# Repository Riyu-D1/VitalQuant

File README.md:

# VitalQuant

### Next-generation biological sensing

VitalQuant is an early-stage biotech research project exploring high-sensitivity
biological sensing using photonics, computational methods, and emerging
quantum-inspired techniques. The goal is to investigate whether better
measurement plus better computation can surface subtle biological changes
earlier than conventional approaches.

> **Status:** Early-stage research & prototype development.
> **Not a medical device or diagnostic system** — model outputs are
> experimental anomaly scores only.

## Repository layout

This is the VitalQuant monorepo — all VitalQuant work in one place:

```
hardware/pcb/        fix_v25 board (ESP32-S3-WROOM-1-N16R8) — fix_v24 plus
                     12 probe test points (TP29-TP40, top side, DNP); DRC
                     0 errors / 0 unconnected / 0 shorts / 0 parity, ERC 0,
                     KiCad 10.0.4; fab zip in hardware/pcb/fab/ —
                     see hardware/README.md
hardware/case/       V10 enclosure design (passes CAD checks; nothing
                     printed, no physical fit validation)
                     — layout detail in hardware/README.md
firmware/esp32/      sensor driver contract + hw_v0/hw_v1/hw_v2 profiles
firmware/vitalquant/ firmware v2 for ESP32-S3 (sensors, model, cloud, power)
                     + POSIX host board simulator
web/                 VitalQuant website (Vite + React 19 + Tailwind + three.js)
software/            Python platform + services:
                     src/vitalquant/    core: ingest, processing, ml, quantum, synth, datasets
                     apps/          service entrypoints (FastAPI, pipeline worker, Streamlit)
                     tests/         unit and ingestion test suite
                     supabase/      Postgres DDL migrations (native partitioning)
                     config/        hardware profile examples
                     simulations/   standalone research simulations
                     pyproject.toml, docker-compose.yml, .env.example
docs/                design rationale: spec audit → research → architecture → schema
                     → API → pipeline → ML plan → quantum-sim design → roadmap;
                     docs/FUNDER_SUMMARY.md — one-page status for reviewers
JOURNAL.md           hardware/sensor research log
.github/workflows/   CI
```

## Platform quickstart (local, no hardware)

```bash
pip install -e ".[ingest,processing,ml,dashboard,dev]"
docker compose up -d db                      # local Postgres 17
export DATABASE_URL=postgresql://vitalquant:vitalquant@localhost:5432/vitalquant
vitalquant-migrate                               # apply supabase/migrations
vitalquant-device --label bench-01 --hardware-revision hw_v0   # prints device key once
export VITALQUANT_DEVICE_KEY=vq_...

uvicorn vitalquant.ingest.app:app --port 8000 &  # API
vitalquant-synth --profile config/hardware.example.yaml --duration 120 \
    --api http://localhost:8000              # synthetic device → API → DB
vitalquant-worker --all                          # → quality + features
streamlit run apps/dashboard/app.py          # dashboard
```

## Website

```bash
cd web
npm ci
npm run dev      # Vite dev server
npm run build    # production build → web/dist
```

## License

Source-available for **Hack Club review only** — not open source.
See [LICENSE](LICENSE).

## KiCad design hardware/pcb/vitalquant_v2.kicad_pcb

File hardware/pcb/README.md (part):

# VitalQ hw_v1

Research prototype. This is not a medical device. Nothing here is a claim
about safety, sterility, biocompatibility, or regulatory clearance.
The defibrillator parts are not an IEC 60601-2-27 type-test claim.
The 51 kΩ pulse resistors are a research-prototype attempt to follow
the TI pulse guidance. They do not make this a defibrillator-proof
medical input. The gas-discharge tubes were removed.

The schematic is drawn explicitly. The PCB is a partial route on a
**36.5 × 70.0 mm** rectangle, **4 layers**, parts on both sides.
Six layers were not required. The stackup intent is JLCPCB
JLC04161H-7628, 1.6 mm, 1 oz outer and 0.5 oz inner, ENIG, with POFV
via-in-pad on the BGA balls that can escape. Routing is not finished.
`VERIFICATION.md` lists the nets that are still open.

Regenerate and check with `hardware/pcb/check.sh` (KiCad 10.0.4).

The firmware pin map is `PINMAP.md`. Every resistor and capacitor is
in `PASSIVES.md`. Orderable part numbers are in `vitalq_hw_v1_bom.csv`.
Footprint sources are in `lib/SOURCES.md`.

This branch also carries the `hw_v2` specification (`HW_V2_SPEC.md`).
The files in this directory still describe hw_v1 until the regenerated
schematic and board land; see the hw_v2 paragraph in the Board section
and `VERIFICATION.md` §hw_v2.

## What changed from the previous board

One part was replaced. The XC6206P332MR (U3) is now a TI TPS63802
buck-boost, 3.3 V, with the datasheet 0.47 µH inductor and the 10 µF /
22 µF 0603 capacitors. EN is tied to VBAT so the rail exists before the
I/O expander runs. MODE is grounded (power save). The exposed pad is GND.

J4, the off-board PPG pads, is gone. The ams OSRAM SFH 7072 is on the
board, on the skin side. Anodes go to the TPS61240 5 V rail (TX_5V).
Cathodes go to AFE4900 LED1–LED4. The two photodiodes go to two AFE4900
PD inputs. The package has the optical barrier. The footprint does not
cut a slot through the centre: the 0.9 mm pads at ±0.6 mm would overlap
a slot of 0.8 mm or wider. A window outline stays on User.1.

Everything else that was on the previous board is still here, including
R8 and R10. The list is at the bottom of this file.

## Board

The module antenna keep-out is x = 0 to 6.5 mm, every copper layer.
Pads start at x ≥ 6.55 mm. USB-C is rotated so the opening is the right
edge. The buck-boost, the 5 V boost, and the CP2102 sit on
the top, on the right, next to USB. The charger sits on the bottom,
next to the LiPo pads, away from the TMP117s. The flash, the IMU, the BME280, and
the expander are also on the top, below the module. Analog parts are on
the bottom, away from that switcher column.

Skin side, one cluster: SFH 7072, the
AS7341 with the white LED and the 860 nm LED about 5 mm from the
aperture, and the MLX90632. A 1.0 mm slot separates those LEDs from the
AS7341. J5 and J6 sit on the bottom and top edges of that cluster.
U11 is on a slotted island beside the LEDs. U20 is on the top at the
same XY, outside the module body. The island neck faces the cluster.

Above that cluster, five 2512 pulse resistors (R32–R36) are on the
bottom and four more (R76–R79) are on the top at the same X. The LiPo
pads and the charger are on the bottom, past that row. Four more 2512s
(R80–R83) are the chest bio-impedance leads, on the bottom past the
charger, because a turned 2512 does not fit in the gap that is already
there. There is no gas-discharge tube.

Electrodes are flat solder pads. No headers. J5 is five pads: ADS1292R
positive, ADS1292R negative, RLD, AFE4900 positive, AFE4900 negative.
J6 is the four EDA pads. The EDA cable is a flex tail to the shoulder.
The electrodes on that tail must land at least 5 cm from the ECG
electrodes. That distance is on the harness, not on this board.
J7 is four chest pads for the AD5940 4-wire respiration measurement
(F+, F−, S+, S−). They are not tied to J5 or J6.

The creepage slots between the 2512 electrode pads are 1.0 mm wide,
including the R35–R36 gap and the three gaps between R80–R83. On a
1.6 mm board the path down one face, across the slot, and up the other
face is 4.2 mm. The straight copper gap between adjacent 2512 pads is
still 3.10 mm: five 3.35 mm pads and four wider gaps do not fit in the
36.5 mm width once the antenna keep-out is reserved. J5 is still 0.55 mm
between pads, and J6 and J7 are still 1.05 mm. A custom rule asks for
1.5 mm from each high-voltage electrode net to unrelated copper. DRC
still reports that rule. Adjacent electrode pads are not 1.5 mm apart.

Placement was repacked after review: all 245 parts kept, none removed.
Every skin-facing sensor stays on the bottom in one cluster — the ECG
pads (J5), SFH 7072, MLX90632, AS7341, both LEDs, and the TMP117 pair
sit inside a ~16 × 16 mm window around the same skin spot. The 860 nm
LED (D11) was moved beside the white LED so both emitters light the
same aperture. Each IC's passives were pulled tight against it: the
AFE4900 supply/reference network (C16–C27, C42, R11–R13) wraps U7 on
the bottom, the ADS1292R input/RLD network (R14–R31, R67–R69,
C28–C35, C43, C48–C53, C65–C66) hugs U8, and the AD5940 loop plus the
isolated electrode path (C56–C57, C15, R43–R45, C54–C55, R39–R42,
D6–D9) sit at U6 and along the J6 corridor. U9's I2C pull-ups now
flank the expander, and the USB-UART series resistors moved beside the
connector row. Placement gates are clean: 0 courtyard clashes, 0
pad-to-slot/edge hits, 0 SMD-vs-through-hole hits, 0 missing pads.

The board is partly routed. Freerouting stalled, and a later maze pass
that shorted nets was discarded. `VERIFICATION.md` lists every remaining
unconnected net. Design rules are in `vitalq_hw_v1.kicad_pro` and
`vitalq_hw_v1.kicad_dru`: 0.09 mm is the BGA floor, 0.127 mm is the
clearance outside that area, copper-to-edge is 0.3 mm, and the mask web
is 0.1 mm. Reference designators are hidden. Fab reference text is 0.35 mm.

hw_v2 is specified on this branch (`HW_V2_SPEC.md`, authoritative) and is
**placed but unrouted**; everything above still describes hw_v1. In
short: U1 becomes an ESP32-S3-MINI-1U-N4R2 with a U.FL antenna — the
x < 6.5 mm keep-out strip goes away — and native USB on GPIO19/20 takes
over J1 through the fitted R102/R103 0 Ω straps, while the CP2102 console
stays on UART0 and can take the USB pair instead through the DNP R104/R105
straps (never fit both pairs). Adds: a MAX86178 WLP-49 synchronised ECG/PPG/BioZ
AFE that also drives a satellite-PPG tail (J10), an SHT45 skin RH + temp
sensor at 0x44 on the bottom face, a 730 nm LED (D12) paired with the
AS7341 NIR channel, a distal-temperature tail (J9, sensor at 0x4A), a
RESEARCH-GRADE sweat-electrode site (J11), a DNP unified 14-pos FFC tail
(J12), a DNP ECG pad pair for the MAX86178 (J13), a DNP RTC (0x52), a DNP
PDM mic, and a foam insulation dome over U20 for
the core-temperature trend channel (assembly note only). Nothing is
removed — the defib ladder, TP1–TP28, J8, and the whole power tree stay.
The placed outline is **40.0 × 62.0 mm** (291 parts): it grew 8 mm east
from the ~32 mm target to host the J11/J13 HV-boundary protection row
— J10 and J11 sit on the new east edge, and their 0 Ω cut-points
R118–R122 are 2512 HV-boundary parts like the defib ladder. `check.sh`
passes end-to-end (ERC 0, placement gates 0, 499 unconnected nets plus
9 waived intra-package clearances) but the board is **unrouted and not
fabrication-ready**. Full design doc:
`../../docs/10-hw-v2-upgrade.md`; BOM delta: `BOM_V2_ADDENDUM.md`.

## Part count

**245 parts.** U2 is a BQ25170DSGR in place of the MCP73831. Q3 is
the auto-program pair. D12–D20, the gas-discharge tubes, are gone.
The chest bioZ path adds J7, R80–R87, C67–C70, and D21–D24.
This prefab round adds U21, D25, SW1, SW2, J8, R88–R101, TP1–TP27,
FID1–FID6, H1, and H2.

| Group | Qty | Parts |
| --- | --- | --- |
| ICs | 21 | U1–U21. U2 is BQ25170DSGR. U21 is USBLC6-2SC6 |
| MOSFETs | 2 | Q1 and Q2, both CSD13380F3T |
| Transistor | 1 | Q3 BC847BS,115, SOT-363 |
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
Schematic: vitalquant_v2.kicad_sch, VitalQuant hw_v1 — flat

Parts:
C1, C47: 4.7u; C_0603_1608Metric; LCSC C1705
C2, C20: 4.7u; C_0402_1005Metric; LCSC C23733
C3, C4, C6, C11, C14, C16, C19, C26, C32, C33, C42, C43, C63, C64, C66, C79, C80, C82, C83, C84: 1u; C_0402_1005Metric; LCSC C52923
C7, C45: 22u; C_0603_1608Metric; LCSC C86295
C8, C13, C15, C18, C24, C25, C27, C28, C29, C36, C37, C38, C39, C40, C41, C50, C51, C56, C57, C58, C59, C60, C61, C62, C76, C77, C78, C81, C86, C88, C90, C91: 100n; C_0402_1005Metric; LCSC C1525
C9, C30, C87: 10u; C_0402_1005Metric; LCSC C15525
C10: 1u; C_0603_1608Metric; LCSC C15849
C21, C22, C23, C55, C68, C69, C70: 470n; C_0402_1005Metric; LCSC C47339
C34: 47n; C_0402_1005Metric; LCSC C6261448
C35: 4.7n; C_0402_1005Metric; LCSC C84705
C44, C89: 10u; C_0603_1608Metric; LCSC C19702
C46: 2.2u; C_0402_1005Metric; LCSC C444845
C48, C49, C52, C53: 2.2n; C_0402_1005Metric; LCSC C84703
C54, C67: 15n; C_0402_1005Metric; LCSC C114405
C65: 1.5n; C_0402_1005Metric; LCSC C23967
C85: 47u; C_0603_1608Metric; LCSC C730416
D1, D2, D3, D4, D5, D6, D7, D8, D9, D21, D22, D23, D24, D26, D27, D28: TPD1E10B06; TPD1E10B06_DPY; LCSC C48260
D10: NF2W757G-F1; NF2W757G; Manufacturer_Part_Number NF2W757G-F1
D11: SFH4053; LED_0402_1005Metric; LCSC C2900307
D12: XL0603NRC730; LED_0603_1608Metric
D25: KT-0603G; LED_0603_1608Metric; LCSC C12624
D29, D30: TPD1E10B06; TPD1E10B06_DPY; LCSC C48260; not fitted
D33: 1N5819WS; D_SOD-323; LCSC C191023
FID1, FID2, FID3, FID4, FID5, FID6: FID; Fiducial_1mm
H1, H2: M2; MountingHole_2.2mm_M2
J1: USB-C; USB_C_Receptacle_HRO_TYPE-C-31-M-12; LCSC C165948
J2: LiPo pads; Pads_LiPo
J3: FSR pads; Pads_FSR
J5: ECG pads; Pads_ECG
J6: EDA pads; Pads_EDA
J7: Chest bioZ; Pads_BIOZ
J8: TC2030; Tag-Connect_TC2030-IDC-NL_2x03_P1.27mm_Vertical
J9: I2C tail pads; Pads_1x04
J10: Optical tail pads; Pads_1x06
J11: Sweat site; Pads_1x03
J12: FH12-14S; Hirose_FH12-14S-0.5SH_1x14-1MP_P0.50mm_Horizontal; LCSC C5378715
J13: MX ECG pads; Pads_1x02; not fitted
L1: 0.47u; L_DFE201612E; LCSC C668312
L2: 1.0u; L_DFE201612E; LCSC C337892
Q1, Q2, Q4: CSD13380F3T; Texas_PicoStar_DFN-3_0.69x0.60mm; LCSC C2871092
Q3: BC847BS,115; SOT-363_SC-70-6; Manufacturer_Part_Number BC847BS-7-F; LCSC C156292
Q6: AO3401A; SOT-23; LCSC C15127
R1, R2: 5.1k; R_0402_1005Metric; LCSC C25905
R3: 1.5k; R_0402_1005Metric; LCSC C25867
R5, R6, R7, R8, R9, R11, R14, R49, R52, R53, R60, R65, R67, R68, R69, R70, R71, R72, R73, R74, R98, R100, R101, R112, R113, R115, R116, R117: 10k; R_0402_1005Metric; LCSC C25744
R10, R13, R39, R40, R41, R42, R62, R84, R85, R86, R87: 1k; R_0402_1005Metric; LCSC C11702
R12: 10; R_0402_1005Metric; LCSC C25077
R15, R16, R17: 1M; R_0402_1005Metric; LCSC C26083
R18: 200k; R_0402_1005Metric; LCSC C25764
R19, R20, R21, R22: 2.2k; R_0402_1005Metric; LCSC C25879
R23: 560k; R_0402_1005Metric; LCSC C132339
R24, R25, R44, R46, R48, R50, R59, R99, R110, R123: 100k; R_0402_1005Metric; LCSC C25741
R26, R27, R28, R29: 10M; R_0402_1005Metric; LCSC C26082
R30, R31: 40.2k; R_0402_1005Metric; LCSC C25893
R32, R33, R34, R35, R36, R76, R77, R78, R79, R80, R81, R82, R83, R120, R121, R122: 51k; R_2512_6332Metric; LCSC C30412
R43, R45: 5.11M; R_0402_1005Metric; LCSC C407678
R47, R109: 100; R_0402_1005Metric; LCSC C25076
R51: 150k; R_0402_1005Metric; LCSC C25755
R61: NTC 10k B3380; R_0402_1005Metric; LCSC C77131
R63: 22.1k; R_0402_1005Metric; LCSC C43473
R64: 47.5k; R_0402_1005Metric; LCSC C25896
R66: 301k; R_0402_1005Metric; LCSC C102962
R75: 27.0k; R_0402_1005Metric; LCSC C25771
R88: 150; R_0402_1005Metric; LCSC C25082
R89, R90, R91, R92, R95, R96, R97, R102, R103, R106, R114: 0; R_0402_1005Metric; LCSC C17168
R93: 0; R_0603_1608Metric; LCSC C21189; not fitted
R94: 0; R_0603_1608Metric; LCSC C21189
R104, R105: 0; R_0402_1005Metric; LCSC C17168; not fitted
R107, R108: 100k; R_0402_1005Metric; LCSC C25741; not fitted
R118, R119: 51k; R_2512_6332Metric; LCSC C30412; not fitted
SW1, SW2: TS-1088; SW_SPST_TS-1088-xR020; LCSC C720477
TP1: VBUS; TestPoint_Pad_D1.0mm
TP2: VBAT; TestPoint_Pad_D1.0mm
TP3: +3V3; TestPoint_Pad_D1.0mm
TP4: +1V8; TestPoint_Pad_D1.0mm
TP5: TX_5V; TestPoint_Pad_D1.0mm
TP6: VDD_CP2102; TestPoint_Pad_D1.0mm
TP7, TP8: GND; TestPoint_Pad_D1.0mm
TP9: ESP_EN; TestPoint_Pad_D1.0mm
TP10: ESP_IO0; TestPoint_Pad_D1.0mm
TP11: ESP_TX; TestPoint_Pad_D1.0mm
TP12: ESP_RX; TestPoint_Pad_D1.0mm
TP13: I2C_SDA; TestPoint_Pad_D1.0mm
TP14: I2C_SCL; TestPoint_Pad_D1.0mm
TP15: I2C_SDA_1V8; TestPoint_Pad_D1.0mm
TP16: I2C_SCL_1V8; TestPoint_Pad_D1.0mm
TP17: SPI_SCK; TestPoint_Pad_D1.0mm
TP18: SPI_MOSI; TestPoint_Pad_D1.0mm
TP19: SPI_MISO; TestPoint_Pad_D1.0mm
TP20: CS_ADS1292; TestPoint_Pad_D1.0mm
TP21: CS_AFE4900; TestPoint_Pad_D1.0mm
TP22: CS_AD5940; TestPoint_Pad_D1.0mm
TP23: CS_FLASH; TestPoint_Pad_D1.0mm
TP24: ADS1292_DRDY; TestPoint_Pad_D1.0mm
TP25: AFE4900_ADC_RDY; TestPoint_Pad_D1.0mm
TP26: EXP_INT; TestPoint_Pad_D1.0mm
TP27: CHG_STAT; TestPoint_Pad_D1.0mm
TP28: RTC_INT; TestPoint_Pad_D1.0mm
TP29: RLDREF; TestPoint_Pad_D1.0mm; not fitted
TP30: RLDOUT; TestPoint_Pad_D1.0mm; not fitted
TP31: VBAT_SYS; TestPoint_Pad_D1.0mm; not fitted
TP32: +3V3_ANA; TestPoint_Pad_D1.0mm; not fitted
TP33: TX_5V_RAW; TestPoint_Pad_D1.0mm; not fitted
TP34: RTC_VBK; TestPoint_Pad_D1.0mm; not fitted
TP35: +3V3_ESP; TestPoint_Pad_D1.0mm; not fitted
TP36: IOVDD; TestPoint_Pad_D1.0mm; not fitted
TP37: CHG_ISET; TestPoint_Pad_D1.0mm; not fitted
TP38: CHG_VSET; TestPoint_Pad_D1.0mm; not fitted
TP39: VBUS_DET; TestPoint_Pad_D1.0mm; not fitted
TP40: TS; TestPoint_Pad_D1.0mm; not fitted
U1: ESP32-S3-WROOM-1-N16R8; ESP32_S3_WROOM_1; LCSC C2913202
U2: BQ25170DSGR; Texas_DSG0008A_WSON-8-1EP_2x2mm_P0.5mm_EP0.9x1.6mm; LCSC C5208201
U3: TPS63802DLAR; WSON-10-1EP_2x3mm_P0.5mm_EP0.84x2.4mm; LCSC C2845237
U4: TPS7A2018PDBVR; SOT-23-5; LCSC C963430
U5: CP2102N-A02-GQFN28R; QFN-28-1EP_5x5mm_P0.5mm_EP3.35x3.35mm; LCSC C964632
U6: AFE4900YZR; BGA30N40P5X6_260X210X50; LCSC C2651595
U7: AD5940BCBZ-RL7; BGA56C40P8X7_416X356X55; LCSC C650308
U8: ADS1292RIRSMR; QFN40P400X400X100-33N-D; Manufacturer_Part_Number ADS1292RIRSMR; LCSC C456281
U9: PCA9306DCUR; VSSOP-8_2.3x2mm_P0.5mm; LCSC C33196
U10: AS7341-DLGM; AS7341DLGT; LCSC C2649486
U11, U20: TMP117AIDRVR; TMP117_DRV_NOPASTE; LCSC C699536
U12: MLX90632SLD-DCB-100-RE; MLX90632SLDDCB100SP; Manufacturer_Part_Number MLX90632SLD-DCB-100-RE; LCSC C17235844
U13: BME280; Bosch_LGA-8_2.5x2.5mm_P0.65mm_ClockwisePinNumbering; LCSC C92489
U14: LSM6DSV320XTR; QFN_LSM6DSV80XTR_STM; Manufacturer_Part_Number LSM6DSV320XTR; LCSC C26633007
U15: TPS61240YFFR; TPS61240_YFF; LCSC C2070904
U16: SFH 7072; SFH7072; LCSC C2655172
U17: MAX17048G+T10; TDFN-8-1EP_2x2mm_P0.5mm_EP0.8x1.2mm; LCSC C2682616
U18: W25Q512JVEIQ; W25Q512_WSON8; LCSC C7389628
U19: TCA6408ARSVR; TCA6408A_RSV; LCSC C2649390
U21: USBLC6-2SC6; SOT-23-6; LCSC C7519
U22: MAX86141ENP+; MAX86141_WLP20; LCSC C5328762
U23: SHT45-AD1B; SHT45_DFN4; Manufacturer_Part_Number SHT45-AD1B-R2; LCSC C5221601
U24: RV-3028-C7; RV3028C7; LCSC C2829066
U25: IM69D130; LCSC C536262
U26: SN74AXC2T245RSWR; Texas_RSW0010A_UQFN-10_1.4x1.8mm_P0.4mm; LCSC C1882550

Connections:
+1V8: C36.1, C86.1, C87.1, C88.1, C90.1, R21.1, R22.1, R66.1, R97.2, TP4.1, U9.2 (VREF1), U10.1 (VDD), U22.C2 (VDD_DIG), U22.D2 (VDD_ANA), U26.7 (VCCA), U26.10 (DIR1)
+1V8_LDO: C6.1, R97.1, U4.5 (OUT)
+3V3: C4.1, C37.1, C38.1, C39.1, C40.1, C41.1, C45.1, C59.1, C60.1, C61.1, C76.1, C77.1, C78.1, C81.1, C84.1, C91.1, D10.1 (A), J3.1, J8.1, J9.1, J12.1, R5.1, R6.1, R7.1, R18.1, R19.1, R20.1, R23.1, R47.1, R49.1, R52.1, R53.1, R60.1, R65.1, R74.1, R94.1, R95.1, R98.1, R99.1, R109.1, R112.1, R113.1, R117.1, TP3.1, U3.6 (VOUT), U4.1 (IN), U4.3 (EN), U11.5 (V+), U12.2 (VDD), U13.2 (CSB), U13.6 (VDDIO), U13.8 (VDD), U14.5, U14.8, U14.12, U18.3 (~WP/IO_{2}), U18.7 (~HOLD/~RESET/IO_{3}), U18.8 (VCC), U19.14 (V_{CCP}), U19.15 (V_{CCI}), U20.4 (ADD0), U20.5 (V+), U23.3 (VDD), U24.7 (VDD), U25.2 (VDD), U26.6 (VCCB)
+3V3_ANA: C11.1, C13.1, C16.1, C18.1, C28.1, C29.1, C43.1, C79.1, C80.1, R12.1, R15.1, R26.1, R28.1, R95.2, R116.1, TP32.1, U6.A4 (I2C_SPI_SEL), U6.C1 (RX_SUP), U6.C4 (IO_SUP), U7.A4 (AVDD_1), U7.F2 (AVDD_2), U7.F3 (DVDD), U8.12 (AVDD), U8.14 (CLKSEL), U8.23 (DVDD)
+3V3_ESP: C7.1, C8.1, R94.2, TP35.1, U1.2 (3V3)
AD5940_GPIO0: U1.22 (IO14), U7.F5 (GPIO0)
AD5940_RESET: R11.1, U7.F1 (~RESET), U19.4 (P2)
ADS1292_DRDY: R99.2, TP24.1, U1.38 (IO2), U8.22 (~DRDY)
ADS1292_PWDN: R14.1, U8.15 (~PWDN/~RESET), U19.3 (P1)
ADS_GPIO1: R100.1, U8.26 (GPIO1/RCLK1)
ADS_GPIO2: R101.1, U8.25 (GPIO2/RCLK2)
AFE4900_ADC_RDY: TP25.1, U1.23 (IO21), U6.F4 (ADC_RDY)
AFE4900_RESETZ: R9.1, U6.E1 (RESETZ), U19.2 (P0)
AFE_BG: C15.1, U6.D2 (BG)
AFE_CLK: R10.1, U6.F1 (CLK)
AFE_INM: C57.2, R45.2, U6.A1 (INM_ECG)
AFE_INP: C56.2, R43.2, U6.B1 (INP_ECG)
AFE_N_AC: D5.1, R36.2, R46.1
AFE_N_PAD: J5.5, R36.1
AFE_N_SER: C57.1, R46.2
AFE_P_AC: D4.1, R35.2, R44.1
AFE_P_PAD: J5.4, R35.1
AFE_P_SER: C56.1, R44.2
AIN4_LPF0: C26.1, U7.B4 (AIN4/LPF0)
AVDD_REG: C42.1, U7.D8 (AVDD_REG)
BIOZ_FN: C68.2, U7.D2 (AIN0)
BIOZ_FN_PAD: J7.2, R81.1
BIOZ_FP: R84.2, U7.B3 (AIN1)
BIOZ_FP_PAD: J7.1, R80.1
BIOZ_SN: C70.2, U7.A3 (AIN2)
BIOZ_SN_PAD: J7.4, R83.1
BIOZ_SP: C69.2, U7.B5 (AIN3/BUF_VREF1V8)
BIOZ_SP_PAD: J7.3, R82.1
CE0: R39.2, U7.A7 (CE0)
CE_ISO: C54.2, D6.1, R39.1
CE_SURGE: C54.1, R76.2
CHG_DIS: Q2.1 (G), R59.1, U19.10 (P7)
CHG_ISET: R3.1, TP37.1, U2.2 (ISET)
CHG_PG: R60.2, U1.7 (IO7), U2.6 (~PG)
CHG_STAT: R49.2, TP27.1, U2.5 (STAT), U19.8 (P5)
CHG_VSET: R75.1, TP38.1, U2.7 (VSET)
CP_DTR: Q3.4 (E2), R70.1, U5.28 (~DTR)
CP_RST: R62.2, U5.9 (~RST)
CP_RTS: Q3.1 (E1), R71.1, U5.24 (~RTS)
CP_RX: R72.2, U5.25 (RXD)
CP_TX: R73.1, U5.26 (TXD)
CP_VBUS: R63.2, R64.1, U5.8 (VBUS)
CS_AD5940: R7.2, TP22.1, U1.8 (IO15), U7.F7 (~CS)
CS_ADS1292: R98.2, TP20.1, U1.18 (IO10), U8.18 (~CS)
CS_AFE4900: R116.2, TP21.1, U1.11 (IO18), U6.E3 (SEN)
CS_FLASH: R52.2, TP23.1, U1.9 (IO16), U18.1 (~CS)
CS_MAX86178: R117.2, U1.31 (IO38), U22.A5 (CSB), U26.2 (OE)
DE0: R42.2, U7.B6 (DE0)
DE_SURGE: D9.1, R42.1, R79.2
DVDD_REG: C23.1, U7.G3 (DVDD_REG_1V8)
ECG1_PAD: J5.1, R32.1
ECG2_PAD: J5.2, R33.1
ECG_N: C51.1, C53.1, D2.1, R31.2, R33.2, U8.5 (IN2N)
ECG_P: C50.1, C52.1, D1.1, R30.2, R32.2, U8.6 (IN2P)
EDA_CE_PAD: J6.1, R76.1
EDA_DE_PAD: J6.4, R79.1
EDA_RE_PAD: J6.2, R78.1
EDA_SE_PAD: J6.3, R77.1
ESP_EN: C64.1, J8.5, Q3.6 (C1), R5.2, SW1.1, TP9.1, U1.3 (EN), U19.1 (~RESET)
ESP_IO0: J8.6, Q3.3 (C2), R6.2, SW2.1, TP10.1, U1.27 (IO0)
ESP_RX: J8.4, R73.2, TP12.1, U1.36 (RXD0)
ESP_TX: J8.3, R72.1, TP11.1, U1.37 (TXD0)
EXP_INT: R53.2, TP26.1, U1.15 (IO3), U19.11 (~INT)
FB_3V3: R23.2, R24.1, U3.4 (FB)
FN_ISO: C68.1, D22.1, R85.2
FN_SURGE: R81.2, R85.1
FP_ISO: C67.2, D21.1, R84.1
FP_SURGE: C67.1, R80.2
FSR_ADC: J3.2, R8.1, U1.39 (IO1)
GAUGE_ALRT: R74.2, U1.6 (IO6), U17.5 (ALRT)
GND: C1.2, C2.2, C3.2, C4.2, C6.2, C7.2, C8.2, C9.2, C10.2, C11.2, C13.2, C14.2, C15.2, C16.2, C18.2, C19.2, C20.2, C21.2, C22.2, C23.2, C24.2, C25.2, C26.2, C28.2, C29.2, C30.2, C32.2, C33.2, C36.2, C37.2, C38.2, C39.2, C40.2, C41.2, C42.2, C43.2, C44.2, C45.2, C46.2, C47.2, C48.2, C49.2, C52.2, C53.2, C58.2, C59.2, C60.2, C61.2, C62.2, C63.2, C64.2, C66.2, C76.2, C77.2, C78.2, C79.2, C80.2, C81.2, C82.2, C83.2, C84.2, C85.2, C86.2, C87.2, C88.2, C89.2, C90.2, C91.2, D1.2, D2.2, D3.2, D4.2, D5.2, D6.2, D7.2, D8.2, D9.2, D21.2, D22.2, D23.2, D24.2, D25.2 (K), D26.2, D27.2, D28.2, D29.2, D30.2, J1.A1 (GND), J1.A12 (GND), J1.B1 (GND), J1.B12 (GND), J1.SH (SHIELD), J2.2, J8.2, J9.4, J12.4, Q1.2 (S), Q2.2 (S), Q4.2 (S), R1.2, R2.2, R3.2, R8.2, R9.2, R10.2, R11.2, R14.2, R16.2, R24.2, R25.2, R27.2, R29.2, R48.2, R51.2, R59.2, R61.2, R64.2, R66.2, R75.2, R100.2, R101.2, R108.2, R110.2, R115.2, R123.1, SW1.2, SW2.2, TP7.1, TP8.1, U1.1 (GND), U1.40 (GND), U1.41 (GND), U2.4 (GND), U2.9 (EP), U3.2 (MODE), U3.3 (AGND), U3.8 (GND), U3.11 (EP), U4.2 (GND), U5.3 (GND), U5.29 (GND), U6.B4 (CONTROL1), U6.D1 (RX_GND), U6.D5 (TX_GND), U7.C4 (AGND_1), U7.D5 (AGND_REF)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
I2C_SCL: J9.3, J12.3, R20.2, TP14.1, U1.17 (IO9), U9.6 (SCL2), U11.1 (SCL), U13.4 (SCK), U14.13, U17.7 (SCL), U19.12 (SCL), U20.1 (SCL), U23.2 (SCL), U24.3 (SCL)
I2C_SCL_1V8: R22.2, TP16.1, U9.3 (SCL1), U10.2 (SCL), U12.4 (SCL)
I2C_SDA: J9.2, J12.2, R19.2, TP13.1, U1.12 (IO8), U9.5 (SDA2), U11.6 (SDA), U13.3 (SDI), U14.14, U17.8 (SDA), U19.13 (SDA), U20.6 (SDA), U23.1 (SDA), U24.4 (SDA)
I2C_SDA_1V8: R21.2, TP15.1, U9.4 (SDA1), U10.8 (SDA), U12.1 (SDA)
IN1N: C49.1, R28.2, R29.1, R68.2, U8.3 (IN1N)
IN1N_AC: C51.2, R68.1
IN1P: C48.1, R26.2, R27.1, R67.2, U8.4 (IN1P)
IN1P_AC: C50.2, R67.1
IOVDD: C19.1, R12.2, TP36.1, U7.G2 (IOVDD)
IR_AN: D11.1 (A), R47.2
IR_GATE: Q1.1 (G), R48.1, U19.7 (P4)
IR_K: D11.2 (K), Q1.3 (D)
J11_CE: J11.3, R122.1
J11_RE: J11.2, R121.1
J11_WE: J11.1, R120.1
J13_INM: J13.2, R119.1
J13_INP: J13.1, R118.1
LDR: D10.2 (K), U10.4 (LDR)
LED1_K: J10.1, J12.5, U22.D1 (LED1_DRV)
LED2_K: J10.2, J12.6, U22.C1 (LED2_DRV)
LED3_K: J10.3, J12.7, U22.B1 (LED3_DRV)
LED_A: D25.1 (A), R88.2
LED_AN: J10.4, J12.8, R114.2
LSM6_INT1: U1.4 (IO4), U14.4
MAX86178_INT: R113.2, U1.32 (IO39), U22.B2 (INT)
MIC_CLK: U1.33 (IO40), U25.3 (CLOCK)
MIC_DAT: U1.34 (IO41), U25.1 (DATA)
MISO_AD: R91.1, U7.E8 (MISO)
MISO_ADS: R89.1, U8.21 (DOUT)
MISO_AFE: R90.1, U6.E2 (SDOUT)
MISO_FL: R92.1, U18.2 (DO/IO_{1})
MISO_MX: R106.1, U26.5 (B1)
MX_ECG_INM: D30.1, R119.2
MX_ECG_INP: D29.1, R118.2
MX_SDO_1V8: U22.A3 (SDO), U26.8 (A1)
MX_VREF: C83.1, U22.B5 (VREF)
NIR730_GATE: Q4.1 (G), R110.1, U7.E1 (GPIO2)
NIR_AN: D12.1 (A), R109.2
NIR_K: D12.2 (K), Q4.3 (D)
PD2_INM: U6.B3 (INM2), U16.10 (PD2_A)
PD2_INP: U6.B2 (INP2), U16.3 (PD2_C)
PD_A: J10.6, J12.10, U22.C5 (PD_GND)
PD_INM: U6.A3 (INM), U16.2 (PD1_A)
PD_INP: U6.A2 (INP), U16.1 (PD1_C)
PD_K: J10.5, J12.9, U22.D5 (PD1_IN)
PGA1N: C34.1, U8.1 (PGA1N)
PGA1P: C34.2, U8.2 (PGA1P)
PGA2N: C35.1, U8.7 (PGA2N)
PGA2P: C35.2, U8.8 (PGA2P)
Q3_B1: Q3.2 (B1), R70.2
Q3_B2: Q3.5 (B2), R71.2
RC0_0: C27.1, U7.C8 (RC0_0)
RC0_1: C27.2, U7.B8 (RC0_1)
RCAL0: R13.1, U7.C1 (RCAL0)
RCAL1: R13.2, U7.B1 (RCAL1)
RE0: R41.2, U7.A8 (RE0)
RESP_MODN: R31.1, U8.32 (RESP_MODN/IN3N)
RESP_MODP: R30.1, U8.31 (RESP_MODP/IN3P)
RE_SURGE: D8.1, R41.1, R78.2
RLDINV: C65.2, R17.2, U8.28 (RLDINV)
RLDOUT: C65.1, R17.1, R43.1, R45.1, R69.2, TP30.1, U8.30 (RLDOUT)
RLDREF: C66.1, R15.2, R16.1, TP29.1, U8.29 (RLDIN/RLDREF)
RLD_CLAMP: D3.1, R34.2, R69.1
RLD_PAD: J5.3, R34.1
RTC_INT: R112.2, TP28.1, U24.2 (INT)
RTC_VBK: R115.1, TP34.1, U24.6 (VBACKUP)
SE0: C55.2, U7.A6 (SE0)
SE_ISO: C55.1, D7.1, R40.2
SE_SURGE: R40.1, R77.2
SN_ISO: C70.1, D24.1, R87.2
SN_SURGE: R83.2, R87.1
SPARE_IN: R107.2, R108.1, U1.35 (IO42)
SPI_MISO: R89.2, R90.2, R91.2, R92.2, R106.2, TP19.1, U1.21 (IO13)
SPI_MOSI: TP18.1, U1.19 (IO11), U6.F2 (I2C_DAT), U7.E7 (MOSI), U8.19 (DIN), U18.5 (DI/IO_{0}), U22.A4 (SDI)
SPI_SCK: TP17.1, U1.20 (IO12), U6.F3 (I2C_CLK), U7.F8 (SCLK), U8.20 (SCLK), U18.6 (CLK), U22.A2 (SCLK)
SP_ISO: C69.1, D23.1, R86.2
SP_SURGE: R82.2, R86.1
STATUS_LED: R88.1, U1.10 (IO17)
SWEAT_CE: D28.1, J12.13, R122.2, U7.A1 (AFE4)
SWEAT_RE: D27.1, J12.12, R121.2, U7.A2 (AFE3)
SWEAT_WE: D26.1, J12.11, R120.2, U7.C5 (AIN6)
SW_L1: L1.1, U3.9 (L1)
SW_L2: L1.2, U3.7 (L2)
TMP117_ALERT: R65.2, U1.5 (IO5), U11.3 (ALERT)
TS: J2.3, Q2.3 (D), R61.1, TP40.1, U2.3 (TS)
TX1: U6.D4 (TX1), U16.6 (G1_C)
TX2: U6.E5 (TX2), U16.12 (G2_C)
TX3: U6.E4 (TX3), U16.8 (R_C)
TX4: U6.C5 (TX4), U16.9 (IR_C)
TX5_EN: R25.1, U15.C1 (EN), U19.5 (P3)
TX_5V: C14.1, C89.1, R96.2, R114.1, TP5.1, U6.F5 (TX_SUP), U16.4 (IR_A), U16.5 (G1_A), U16.7 (R_A), U16.11 (G2_A), U22.A1 (VLED)
TX_5V_RAW: C47.1, R96.1, TP33.1, U15.B2 (VOUT), U15.C2 (FB)
TX_SW: L2.2, U15.B1 (L)
USB_CC1: J1.A5 (CC1), R1.1
USB_CC2: J1.B5 (CC2), R2.1
USB_DM: J1.A7 (D-), J1.B7 (D-), R103.1, R105.1, U21.3 (IO2), U21.4 (IO2)
USB_DM_CP: R105.2, U5.5 (D-)
USB_DM_S3: R103.2, U1.13 (IO19)
USB_DP: J1.A6 (D+), J1.B6 (D+), R102.1, R104.1, U21.1 (IO1), U21.6 (IO1)
USB_DP_CP: R104.2, U5.4 (D+)
USB_DP_S3: R102.2, U1.14 (IO20)
VBAT: C2.1, C3.1, C58.1, C82.1, C85.1, J2.1, Q6.3 (D), R93.1, R107.1, TP2.1, U2.8 (OUT), U17.2 (CELL), U17.3 (VDD)
VBAT_SYS: C44.1, C46.1, D33.1 (K), L2.1, Q6.2 (S), R93.2, TP31.1, U3.1 (EN), U3.10 (VIN), U15.A1 (VIN)
VBIAS0: C25.1, U7.C7 (VBIAS0)
VBIAS_CAP: C22.1, U7.D1 (VBIAS_CAP)
VBUS: C1.1, C10.1, C63.1, D33.2 (A), J1.A4 (VBUS), J1.A9 (VBUS), J1.B4 (VBUS), J1.B9 (VBUS), Q6.1 (G), R50.1, R63.1, R123.2, TP1.1, U2.1 (IN), U5.7 (VREGIN), U21.5 (VBUS)
VBUS_DET: R50.2, R51.1, TP39.1, U19.9 (P6)
VCAP1: C32.1, U8.11 (VCAP1)
VCAP2: C33.1, U8.27 (VCAP2)
VDD_CP2102: C9.1, C62.1, R62.1, TP6.1, U5.1 (~DCD), U5.2 (~RI/CLK), U5.6 (VDD), U5.23 (~CTS), U5.27 (~DSR)
VREF2: R18.2, U9.7 (VREF2), U9.8 (EN)
VREFP: C30.1, U8.9 (VREFP)
VREF_1V82: C20.1, U7.A5 (VREF_1V82)
VREF_2V5: C21.1, U7.D7 (VREF_2V5)
VZERO0: C24.1, U7.B7 (VZERO0)

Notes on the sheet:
J13 DNP pads: optional second ECG input pair. R118/R119 + D29/D30 fitted.
J10: LED1/2/3 cathodes, LED anode, PD cathode, PD anode.
I2C and IMU
R13 is RCAL. C27 sits between RC0_0 and RC0_1. XTAL pins are open: the internal oscillator is used.
U23 SHT45-AD1B, 0x44, skin side.
Alternate strap (DNP): move 0R to R104/R105 for the CP2102 bridge.
LED_AN ties to TX_5V through R114 (5 V headroom for green/satellite emitters).
Decoupling, RCAL, RC0
Sheets below contain the parts. They are not empty stubs.
Module decoupling
USB-C, LiPo charger, 3.3 V rail, 1.8 V rail
J12 DNP FFC: pins 1-4 = J9 order, 5-10 = J10 order, 11-13 = J11 order, 14 open.
Charge is on whenever USB is present and TS is in range. CHG_DIS high shorts TS and stops it.
Left: 1.8 V AS7341 behind PCA9306. Right: 3.3 V bus, including the IMU.
Q3 is the DevKitC auto-program pair: DTR/RTS to EN and GPIO0. R70 and R71 are the 10k bases.
Decoupling
POWER & CHARGING (root sheet)
ESP32-S3-WROOM-1-N16R8. On-board PCB antenna: antenna end overhangs the board edge; all-layer keep-out under the on-board sliver. 16 MB flash + 8 MB octal PSRAM inside; IO35/36/37 reserved NC.
I2C sensors and IMU
Test and debug
U3 is a TPS63802 buck-boost. R23/R24 set 3.30 V. C44 and C45 are the datasheet 0603 ceramics. C3 and C4 stay.
D12 is the 730 nm LED; Q4 gate is AD5940 GPIO2 (E1). Pairs with the AS7341 NIR channel.
U4 is the 1.8 V LDO, fed from U3, EN tied to IN. AS7341 VDD is 1.7-2.0 V. Other ICs are 3.3 V.
R61 stays DNP. Fit the cell NTC, not R61 as well. R3 is 1.5k, so charge current is 200 mA.
Straps and FSR
Bias and decoupling
IO26 is the in-module PSRAM select on N4R2. IO33-37, IO47, IO48 are spare GPIO, left open.
AFE4900 PPG and second ECG lead
J7 is F+ F- S+ S-. Dedicated chest pads. Not paralleled onto J5 or J6.
J11 sweat site — RESEARCH-GRADE. WE=AIN6(C5), RE=AFE3(A2), CE=AFE4(A1); VERIFY switch matrix.
MCU
hw_v2: AIN6/AFE3/AFE4 feed J11 (RESEARCH-GRADE sweat site) and GPIO2 is NIR730_GATE. Other GPIO balls stay open.
C16 AVDD, C18 DVDD, C42 AVDD_REG, C19 IOVDD after R12, C20-C26 are the reference and bias caps.
EN has R5 10k and C64 1 uF. Q3 on the USB sheet is the DTR/RTS auto-program pair.
U5/U21/Q3 are unchanged. CP2102 keeps UART0 on ESP_TX/ESP_RX.
Fitted: J1 -> S3 IO20/IO19 (native USB, on-chip JTAG+console).
Other sheets
MAX86178 and tails
J8 Tag-Connect TC2030-NL: 1 +3V3, 2 GND, 3 ESP_TX, 4 ESP_RX, 5 EN, 6 IO0.
U25 IM69D130. PDM on IO40/IO41. 100 nF on VDD (datasheet).

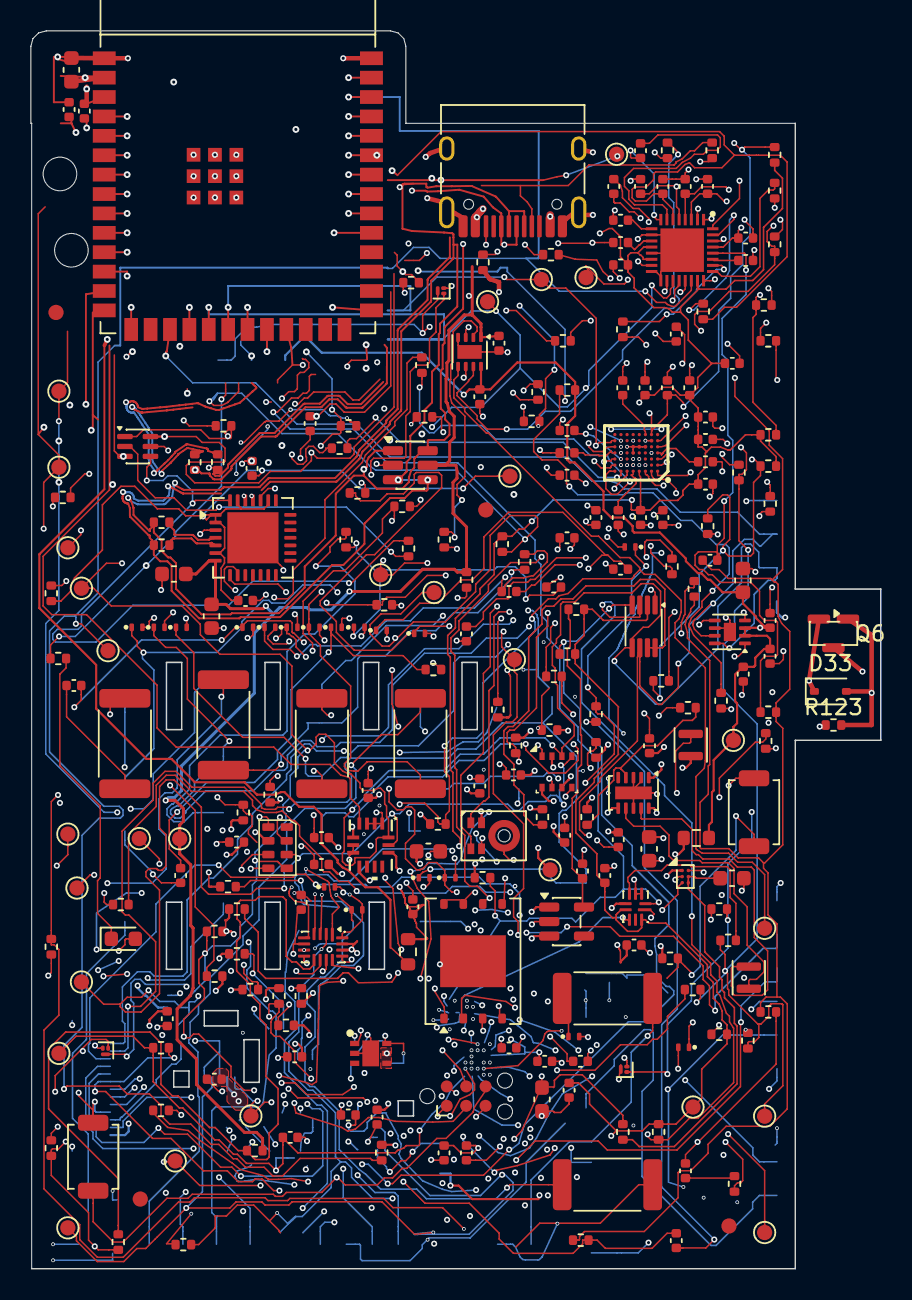
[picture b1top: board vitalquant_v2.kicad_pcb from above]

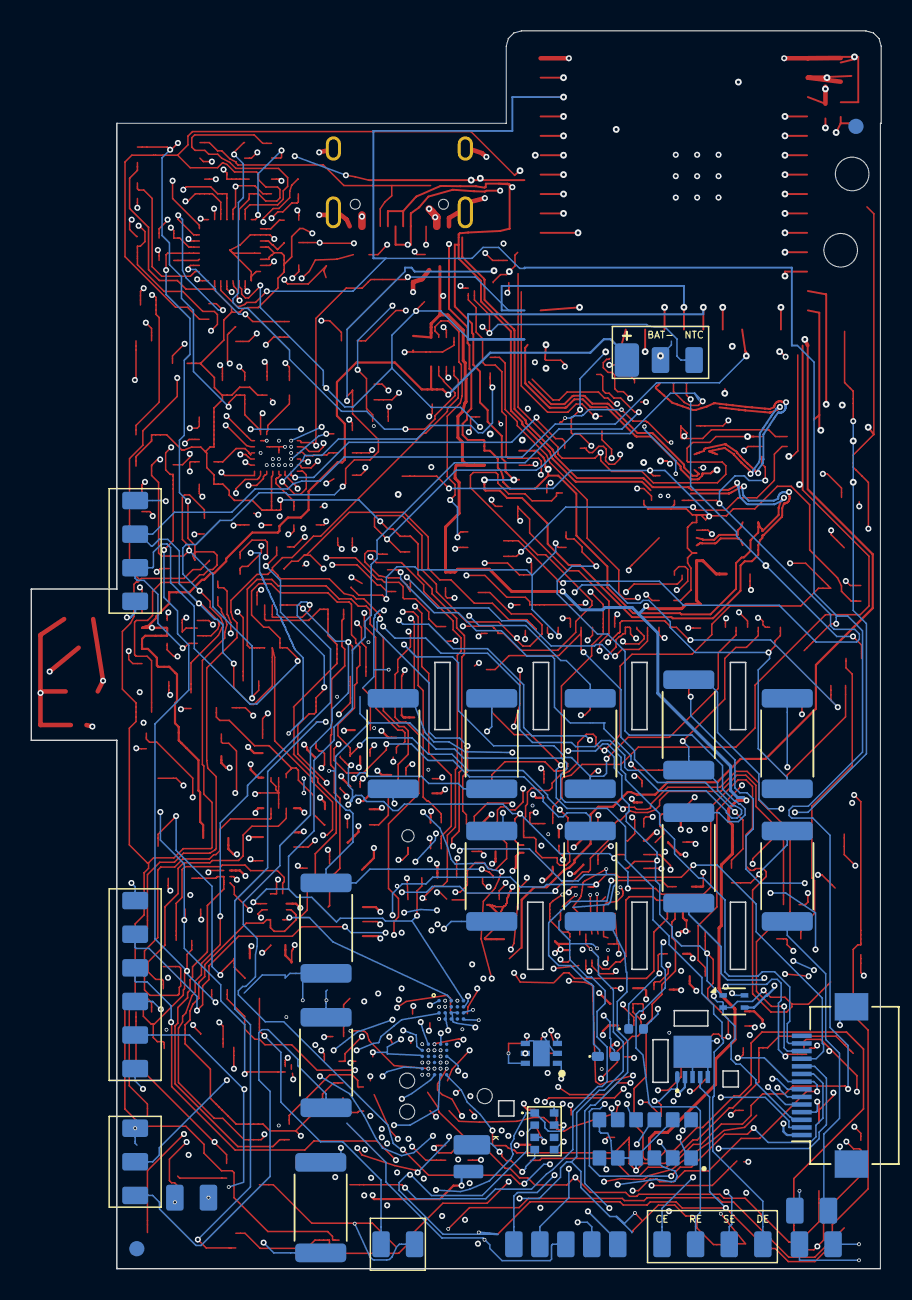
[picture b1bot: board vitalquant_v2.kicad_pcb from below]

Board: 8 copper layers, 55.6 x 81.0 mm, 302 parts (35 on the bottom side), 191 nets.

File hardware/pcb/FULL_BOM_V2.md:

# hw_v2 — Full Board BOM (every component)

292 placed parts on `devin/hw-v2-pcb`. Per single board.
"DNP" = designed in but not populated at assembly.

## ICs & modules — 25

| Ref | Part (orderable MPN) | Package | LCSC | Notes |
|---|---|---|---|---|
| U1 | ESP32-S3-MINI-1-N4R2 | Module 15.4×20.5 | C3013941 | MCU, integrated antenna |
| U2 | BQ25170DSGR | WSON-8 | — | LiPo charger |
| U3 | TPS63802DLAR | WSON-10 | — | Buck-boost +3V3 |
| U4 | TPS7A2018PDBVR | SOT-23-5 | — | 1.8 V LDO |
| U5 | CP2102N-A02-GQFN28R | QFN-28 | — | USB-UART (strap option) |
| U6 | AFE4900YZR | BGA-30 | — | PPG/SpO2 AFE |
| U7 | AD5940BCBZ-RL7 | BGA-56 | C650308 | EDA/BioZ potentiostat |
| U8 | ADS1292RIRSMT | QFN-33 | C882777 | ECG AFE |
| U9 | PCA9306DCUR | VSSOP-8 | — | I2C level shifter |
| U10 | AS7341-DLGM | OLGA-8 | — | Spectral sensor |
| U11, U20 | TMP117AIDRVR | DRV-6 | — | Skin + ambient temp ×2 |
| U12 | MLX90632SLD-DCB-100-SP | SFN-5 | — | IR temperature |
| U13 | BME280 | LGA-8 | — | Ambient P/RH/T |
| U14 | LSM6DSV80XTR | LGA-14 | — | IMU |
| U15 | TPS61240YFFR | DSBGA-6 | — | TX_5V boost |
| U16 | SFH 7072 | Module | C2655172 | Optical emitter+PD |
| U17 | MAX17048G+T10 | TDFN-8 | C2682616 | Fuel gauge |
| U18 | W25Q512JVEIQ | WSON-8 | — | 512 Mbit flash |
| U19 | TCA6408ARSVR | UQFN-8 | C2649390 | GPIO expander |
| U21 | USBLC6-2SC6 | SOT-23-6 | C7519 | USB ESD array |
| U22 | MAX86178ENJ+ | WLP-49 | — | ECG/PPG/BioZ AFE (NDA part) |
| U23 | SHT45-AD1B(-R2) | DFN-4 | — | Humidity/temp |
| U24 | RV-3028-C7 | SON-8 | — | RTC |
| U25 | IM69D130V01XTSA1 | LLGA-5 | — | PDM mic (fitted) |

## Optical emitters — 4

| Ref | Part | Pkg | Qty |
|---|---|---|---|
| D10 | NF2W757G-F1 white LED | NF2W757G | 1 |
| D11 | SFH 4053 IR emitter | 0402 | 1 |
| D12 | SFH 4735 730 nm NIR | 0402 | 1 |
| D25 | KT-0603G green status LED | 0603 | 1 (C12624) |

## ESD / protection — 19

| Part | Refs | Qty fitted | DNP |
|---|---|---|---|
| TPD1E10B06DPYR | D1–D9, D21–D30 | 18 | 0 |
| USBLC6-2SC6 | (listed above, U21) | — | — |

## Connectors / switches — 4 orderable

| Ref | Part | Qty | Status |
|---|---|---|---|
| J1 | TYPE-C-31-M-12 USB-C receptacle | 1 | Fitted |
| J12 | FH12-14S-0.5SH(55) FFC-14 | 1 | DNP |
| SW1, SW2 | TS-1088-AR02016 tactile | 2 | Fitted (C720477) |
| J2,J3,J5,J6,J7,J8,J9,J10,J11,J13 | Solder pads / TC2030 footprint | — | Board features, no orderable part |

## Magnetics — 2

| Ref | Part | Value |
|---|---|---|
| L1 | DFE201612E-R47M | 0.47 µH |
| L2 | DFE201612E-1R0M | 1.0 µH |

## Transistors — 4

| Ref | Part | LCSC |
|---|---|---|
| Q1, Q2, Q4 | CSD13380F3T N-FET PicoStar ×3 | C2871092 |
| Q3 | BC847BS,115 dual NPN SOT-363 | — |

## Capacitors — 72

| MPN | Value / Pkg | Qty fit | DNP | Refs |
|---|---|---|---|---|
| GRM155R71C104KA88 | 100 nF / 0402 | 30 | 0 | C8,C13,C15,C18,C24,C25,C27–C29,C36–C41,C50,C51,C56–C63,C76–C79,C81 |
| GRM155R61A105KE15 | 1 µF / 0402 | 18 | 0 | C3,C4,C6,C11,C14,C16,C19,C26,C32,C33,C42,C43,C64,C66,C80,C82,C83,C84 |
| GRM155R61A474KE15 | 470 nF / 0402 | 7 | 0 | C21–C23,C55,C68–C70 |
| GRM1555C1H222JA01 | 2.2 nF / 0402 | 4 | 0 | C48,C49,C52,C53 |
| GRM155R60J475ME87 | 4.7 µF / 0402 | 3 | 0 | C2,C9,C20 |
| GRM155R71H153KA12 | 15 nF / 0402 | 2 | 0 | C54,C67 |
| CL10A476MQ8NRNC | 47 µF / 0603 | 1 | 0 | C85 (C19702) |
| CL10A226MQ8NRNC | 22 µF / 0603 | 1 | 0 | C7 (C59461) |
| GRM188R61A226ME15 | 22 µF / 0603 | 1 | 0 | C45 |
| CL10A475KA8NQNC | 4.7 µF / 0603 | 1 | 0 | C1 (C69335) |
| GRM188R61A475KE15 | 4.7 µF / 0603 | 1 | 0 | C47 |
| GRM188R61A106ME69 | 10 µF / 0603 | 1 | 0 | C44 |
| GRM155R60J106ME05 | 10 µF / 0402 | 1 | 0 | C30 |
| CL10A105KA8NNNC | 1 µF / 0603 | 1 | 0 | C10 |
| GRM155R60J225ME15 | 2.2 µF / 0402 | 1 | 0 | C46 |
| GRM155R71H473KA88 | 47 nF / 0402 | 1 | 0 | C34 |
| GRM1555C1H472JA01 | 4.7 nF / 0402 | 1 | 0 | C35 |
| GRM1555C1H152JA01 | 1.5 nF / 0402 | 1 | 0 | C65 |

## Resistors — 96

| MPN | Value / Pkg | Qty fit | DNP | Refs |
|---|---|---|---|---|
| RC0402FR-0710KL | 10 kΩ / 0402 | 26 | 0 | R5–R9,R11,R14,R49,R52,R53,R60,R65,R67–R71,R74,R98,R100,R101,R112,R113,R115,R116,R117 (C25744) |
| RC0402FR-071KL | 1 kΩ / 0402 | 14 | 0 | R10,R13,R39–R42,R62,R72,R73,R84–R88 (C11702) |
| DPCR2512-51KJT18 | 51 kΩ / 2512 | 13 | 0 | R32–R36, R76–R83 (HV ladder) |
| 0402WGF0000TCE | 0 Ω / 0402 | 11 | 2 | R89–R92,R95–R97,R102,R103,R106,R114 (+R104,R105) C17168 |
| RC0402FR-07100KL | 100 kΩ / 0402 | 9 | 2 | R24,R25,R44,R46,R48,R50,R59,R99,R110 (+R107,R108) C25741 |
| 25121WJ0000T4E | 0 Ω / 2512 | 5 | 0 | R118–R122 (HV cut-points) C2908946 |
| RC0402FR-074K7L | 4.7 kΩ / 0402 | 4 | 0 | R19–R22 |
| 0402WGF1005TCE | 10 MΩ / 0402 | 4 | 0 | R26–R29 (C26082) |
| RC0402FR-071ML | 1 MΩ / 0402 | 3 | 0 | R15–R17 |
| RC0402FR-075K1L | 5.1 kΩ / 0402 | 2 | 0 | R1,R2 |
| RC0402FR-0740K2L | 40.2 kΩ / 0402 | 2 | 0 | R30,R31 |
| RC0402FR-075M11L | 5.11 MΩ / 0402 | 2 | 0 | R43,R45 |
| RC0402FR-07100RL | 100 Ω / 0402 | 2 | 0 | R47,R109 |
| RC0402FR-07200KL | 200 kΩ / 0402 | 2 | 0 | R18,R51 |
| 0603WAF0000T5E | 0 Ω / 0603 | 2 | 0 | R93,R94 (C21189) |
| RC0402FR-0710RL | 10 Ω / 0402 | 1 | 0 | R12 |
| 0402WGF1501TCE | 1.5 kΩ / 0402 | 1 | 0 | R3 (C25867) |
| RC0402FR-07560KL | 560 kΩ / 0402 | 1 | 0 | R23 |
| NCU15XH103F6SRC | 10 kΩ NTC / 0402 | 0 | 1 | R61 (DNP — cell NTC option) |
| RC0402FR-0722K1L | 22.1 kΩ / 0402 | 1 | 0 | R63 |
| RC0402FR-0747K5L | 47.5 kΩ / 0402 | 1 | 0 | R64 |
| RC0402FR-07301KL | 301 kΩ / 0402 | 1 | 0 | R66 |
| RC0402FR-0727KL | 27 kΩ / 0402 | 1 | 0 | R75 |

## Board features (no part to buy)

- TP1–TP28 test-point pads (28)
- FID1–FID6 fiducials (6)
- H1, H2 M2 mounting holes
- J2/J3/J5/J6/J7/J9/J10/J11/J13 solder-pad fields, J8 TC2030 pads

## Distinct orderable line items: 57
## Totals per board: 285 fitted + 7 DNP placements
(Remaining DNP — all intentional options: R61 cell-NTC, R104/R105 CP2102 USB strap
(mutually exclusive with R102/R103), R107/R108 SPARE divider, J12 FFC, J13 pads)

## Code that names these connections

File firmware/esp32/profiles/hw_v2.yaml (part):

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# ESP32-WROOM-32E → ESP32-S3-MINI-1U-N4R2 (4 MB flash + 2 MB PSRAM, U.FL antenna).
#
# GPIO map (S3-MINI-1U, per spec interface table):
#   GPIO1  FSR_ADC (ADC1_CH0)          GPIO2  ADS1292_DRDY  (timestamped input)
#   GPIO3  EXP_INT (TCA6408, strap)    GPIO4  LSM6_INT1
#   GPIO5  TMP117_ALERT                GPIO6  GAUGE_ALRT
#   GPIO7  CHG_PG                      GPIO8/9  I2C_SDA / I2C_SCL (I2C3V3)
#   GPIO10 CS_ADS1292                  GPIO11/12/13  SPI_MOSI / SPI_SCK / SPI_MISO
#   GPIO14 AD5940_GPIO0 (AD5940 ball F5)  GPIO15 CS_AD5940
#   GPIO16 CS_FLASH (W25Q512)          GPIO17 STATUS_LED (via R88)
#   GPIO18 CS_AFE4900                  GPIO19/20 USB_D- / USB_D+ (native USB-CDC → J1)
#   GPIO21 AFE4900_ADC_RDY (timestamped input)
#   GPIO38 CS_MAX86178                 GPIO39 MAX86178_INT (timestamped input)
#   GPIO40/41 MIC_CLK / MIC_DAT (DNP)  GPIO42 SPARE_IN (digital-only, no ADC — spare input)
#   GPIO43/44 UART0_TX / UART0_RX → CP2102N console (kept)
#   ESP_IO0 / ESP_EN: module pins (SW1/SW2, TP10/TP9; TP24 = ADS1292_DRDY)
#
# USB: native USB-CDC on GPIO19/20 is the DEFAULT strap — R102/R103 (0Ω,
# fitted) route J1 D+/D- to USB_DP_S3/USB_DM_S3. Alternate strap R104/R105
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#   P4 IR_GATE, P5 CHG_STAT, P6 VBUS_DET, P7 CHG_DIS
#
# NIR730_GATE: D12 730 nm LED (+3V3 via R109 100Ω) cathode switched by Q4,
# gated by AD5940 GPIO2 on ball E1 — NOT GPIO0 (GPIO0/ball F5 is the ESP32
# GPIO14 input link, net AD5940_GPIO0). Pairs with the AS7341 nir channel
# for the derived tissue.sto2 ratio.
#
# Tail connectors:
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    model: ADS1292R             # ECG + respiration; defib-protection ladder kept
    bus: spi1
    cs: 10                      # CS_ADS1292
    int_pin: 2                  # ADS1292_DRDY — timestamped input
    outputs: [ecg.ii, resp.waveform]
    sample_rate_hz: 500

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    model: AFE4900              # main SpO2 PPG → SFH7072 optical front-end (kept)
    bus: spi1
    cs: 18                      # CS_AFE4900
    int_pin: 21                 # AFE4900_ADC_RDY — timestamped input
    channels:
      - { id: ppg.red, wavelength_nm: 660, led_driver: 1, pd: 0 }
      - { id: ppg.ir,  wavelength_nm: 940, led_driver: 2, pd: 1 }
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    model: MAX86178             # synchronized ECG/PPG/BioZ AFE; hw_v2 duty = satellite PPG tail J10
    bus: spi1
    cs: 38                      # CS_MAX86178
    int_pin: 39                 # MAX86178_INT — timestamped input
    channels:
      # SFH7050A emitters on J10 time-mux onto the single ppg.satellite stream;
      # led_driver = MAX86178 LED1/2/3 cathode pad. VERIFY wavelength set vs BOM.
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    model: AD5940               # EDA / bioZ-lactate duty (kept); reset via expander P2
    bus: spi1
    cs: 15                      # CS_AD5940
    # also owns NIR730_GATE — AD5940 GPIO2 on ball E1 (not GPIO0/ball F5)
    outputs: []                 # EDA/bioZ waveform channel ids pending registration

  sweat:
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                                # three: 0x48 U11 skin, 0x49 U20 under the
                                # insulation dome (ZHF pair → core.temp_est),
                                # 0x4A distal on J9 tail → skin.temp_distal.
                                # TMP117_ALERT = GPIO5
    outputs: [core.temp_est, skin.temp_distal]
    rate_hz: 1

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  contact:
    enabled: true
    model: FSR402               # kept — FSR pads
    input: adc1_ch0             # FSR_ADC = GPIO1 — ordinal level, no SI units
    outputs: [contact.level]
    rate_hz: 20

  gauge:
    enabled: true
    model: MAX17048             # fuel gauge, power tree kept; GAUGE_ALRT = GPIO6
    bus: i2c0
    address: "0x36"
    int_pin: 6
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
  expander:
    enabled: true
    model: TCA6408              # P0-P7 map in header comment; EXP_INT = GPIO3
    bus: i2c0
    address: "0x20"
    int_pin: 3
    outputs: []                 # GPIO only — owns resets/PWDN/TX5_EN/IR_GATE/charge ctl

  flash:
    enabled: true
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
power_profile: battery            # gates duty cycling + wifi burst strategy
storage:
  offline_buffer: flash_ring      # W25Q512 (CS_FLASH = GPIO16)
  buffer_capacity_s: 1800

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
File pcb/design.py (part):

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    sh.text("R63/R64 are the Rev 1.5 Fig 2.5 divider. VREGIN is still the USB 5 V pin.", 40, 187, 1.4)
    sh.text("C9+C62 on VDD, C1+C63 on VREGIN: 4.7 uF and 100 nF on each regulator pin.", 40, 193, 1.4)
    sh.text("R72 and R73 are 1k in series with TX and RX so an unpowered side is not back-driven.", 40, 199, 1.3)
    sh.text("Q3 is the DevKitC auto-program pair: DTR/RTS to EN and GPIO0. R70 and R71 are the 10k bases.", 40, 205, 1.3)


def mcu(d: Design):
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        "29": "CS_AFE4900",
        "14": "NC",
        "16": "AFE4900_ADC_RDY",
        "13": "AD5940_GPIO0",
        "23": "CS_AD5940",
        "28": "STATUS_LED",  # GPIO17. N8R2 note 3 reserves only IO16 for PSRAM.
        "30": "SPI_SCK",
        "31": "SPI_MISO",
        "33": "I2C_SDA",
        "36": "I2C_SCL",
        "37": "SPI_MOSI",
        "10": "GAUGE_ALRT",  # GPIO25, not a strap
        "11": "CS_FLASH",
        "12": "CHG_PG",  # GPIO27, digital input
        "8": "LSM6_INT1",
        "9": "TMP117_ALERT",
        "6": "ADS1292_DRDY",
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    d.finish(sh, exp)
    d.vpart(sh, "C", "C60", "100n", FP_C, 390, 250, "+3V3", "GND")

    sh.text("GPIO2 and GPIO12 are open so the straps stay low. GPIO15 (CS_AD5940) is pulled up.", 16, 200, 1.4)
    sh.text("GPIO6-11 are the module flash bus and have no symbol pins. ADC1 is GPIO36 and GPIO39.", 16, 208, 1.4)
    sh.text("EN has R5 10k and C64 1 uF. Q3 on the USB sheet is the DTR/RTS auto-program pair.", 16, 216, 1.4)
    sh.text("R7 is the only chip-select pull-up. It is required because GPIO15 must be high at reset.", 16, 224, 1.4)
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        "B1": "AFE_INP",
        "A2": "PD_INP",
        "A3": "PD_INM",
        "B2": "PD2_INP",
        "B3": "PD2_INM",
        "B5": "NC",
        "A5": "NC",
        "C2": "NC",  # RLD_OUT stays off
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    opt = d.part(sh, "SFH7072", "U16", "SFH 7072", FP_SFH, 70, 90, labels="ic")
    d.stub_net(sh, opt, "1", "PD_INP", 7.62)
    d.stub_net(sh, opt, "2", "PD_INM", 7.62)
    d.stub_net(sh, opt, "3", "PD2_INP", 7.62)
    d.stub_net(sh, opt, "10", "PD2_INM", 7.62)
    d.join_row(sh, opt, ["4", "5", "7", "11"], "TX_5V", 7.62)
    d.stub_net(sh, opt, "6", "TX1", 7.62)
    d.stub_net(sh, opt, "12", "TX2", 7.62)
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        "F2": "+3V3_ANA",
        "F3": "+3V3_ANA",
        "F4": "NC",
        "F5": "AD5940_GPIO0",
        "F6": "NC",
        "F7": "CS_AD5940",
        "F8": "SPI_SCK",
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    d.flag_net(sh, "IOVDD", 175, 203)

    sh.text("C16 AVDD, C18 DVDD, C42 AVDD_REG, C19 IOVDD after R12, C20-C26 are the reference and bias caps.", 16, 236, 1.35)
    sh.text("R13 is RCAL. C27 sits between RC0_0 and RC0_1. XTAL pins are open: the internal oscillator is used.", 16, 242, 1.35)
    # Surge resistor on the pad, then the AN-1557 network. C54 is behind R76.
    d.hpart(sh, "R", "R76", "51k", FP_HV, 200, 210, "EDA_CE_PAD", "CE_SURGE")
    d.hpart(sh, "C", "C54", "15n", FP_C, 255, 210, "CE_SURGE", "CE_ISO")
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    d.vpart(sh, "D_TVS_2", "D8", "TPD1E10B06", FP_TVS, 400, 202, "RE_SURGE", "GND")
    d.vpart(sh, "D_TVS_2", "D9", "TPD1E10B06", FP_TVS, 400, 228, "DE_SURGE", "GND")
    sh.text("R76-R79 are the pad-side 51k DPCR. C54 sits behind R76. R39 stays the 1k RLIMIT. No gas tube.", 16, 268, 1.3)
    sh.text("AIN6, the AFE balls, and the unused GPIO balls stay open. GPIO0 is the only digital sideband.", 16, 274, 1.3)
    # Chest 4-wire. Same pad-side order as EDA. Force uses the Fig 54 15 nF and 1 kΩ.
    # The other three lines use 470 nF. 26 mm keeps a TPD GND stub off the next label.
    d.hpart(sh, "R", "R80", "51k", FP_HV, 230, 114, "BIOZ_FP_PAD", "FP_SURGE")
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        "20": "SPI_SCK",
        "21": "MISO_ADS",
        "22": "ADS1292_DRDY",
        "25": "ADS_GPIO2",
        "26": "ADS_GPIO1",
        "33": "GND",  # exposed pad, must be AVSS
    }
    d.side_map(sh, u, side, 8.89)
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    d.hpart(sh, "R", "R17", "1M", FP_R, 175, 240, "RLDOUT", "RLDINV")
    d.hpart(sh, "C", "C65", "1.5n", FP_C, 230, 200, "RLDOUT", "RLDINV")
    d.vpart(sh, "C", "C66", "1u", FP_C, 175, 155, "RLDREF", "GND")
    d.vpart(sh, "R", "R100", "10k", FP_R, 210, 155, "ADS_GPIO1", "GND")
    d.vpart(sh, "R", "R101", "10k", FP_R, 235, 155, "ADS_GPIO2", "GND")

    # Fig 68. Electrode node is ECG_P / ECG_N, after the series resistor.
    d.vpart(sh, "R", "R26", "10M", FP_R, 250, 185, "+3V3_ANA", "IN1P")
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
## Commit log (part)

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2026-03-24 feat: initial commit
2026-04-02 Update site content, images and fix simulation logic
2026-04-05 Fix recursive submodule issue and add recent changes
2026-04-05 Fix Netlify build by pinning tailwindcss to 3.4.17
2026-04-05 Enforce Node 20.x for Netlify builds
2026-04-05 Remove listed future application items from About page
2026-04-05 Update Advisors section text
2026-04-05 Remove contact card from About page
2026-04-05 mobile
2026-04-05 Update Navbar with responsive mobile sidebar menu using React syntax
